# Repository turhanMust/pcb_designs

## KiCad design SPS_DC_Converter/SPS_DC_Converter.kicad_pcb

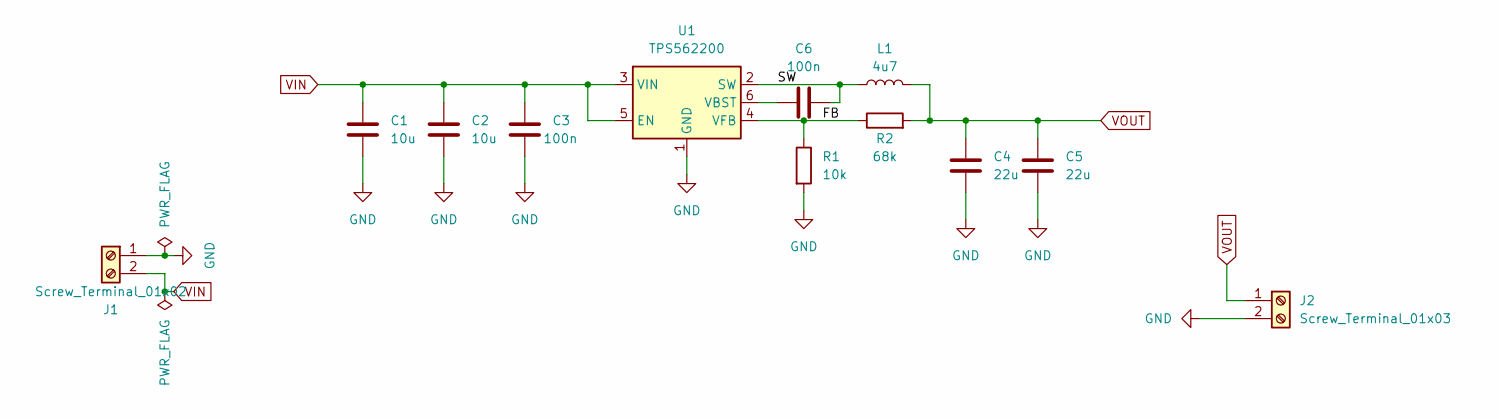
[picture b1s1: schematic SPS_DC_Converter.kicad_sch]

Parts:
C1, C2: 10u; C_0805_2012Metric
C3, C6: 100n; C_0603_1608Metric
C4, C5: 22u; C_1206_3216Metric
J1: Screw_Terminal_01x02; TerminalBlock_bornier-2_P5.08mm
J2: Screw_Terminal_01x03; TerminalBlock_bornier-2_P5.08mm
L1: 4u7; L_Vishay_IHLP-2525
R1: 10k; R_0805_2012Metric
R2: 68k; R_0805_2012Metric
U1: TPS562200; SOT-23-6

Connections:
/FB: R1.1, R2.1, U1.4 (VFB)
/SW: C6.2, L1.1, U1.2 (SW)
GND: C1.2, C2.2, C3.2, C4.2, C5.2, J1.1, J2.2, R1.2, U1.1 (GND)
unnamed: C6.1, U1.6 (VBST)
VIN: C1.1, C2.1, C3.1, J1.2, U1.3 (VIN), U1.5 (EN)
VOUT: C4.1, C5.1, J2.1, L1.2, R2.2

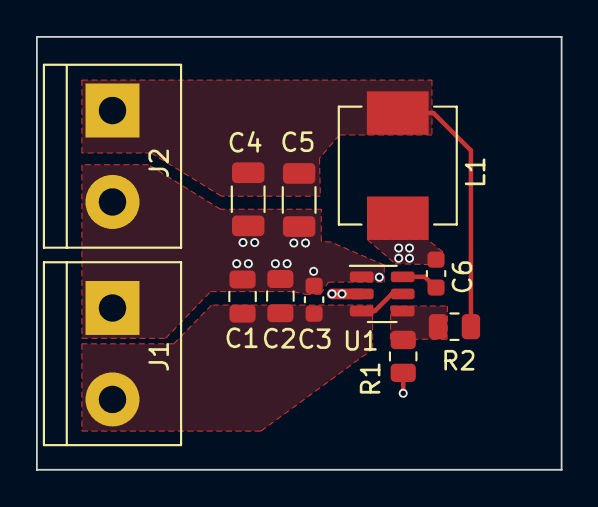
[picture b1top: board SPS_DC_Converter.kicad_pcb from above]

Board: 2 copper layers, 29.1 x 24.0 mm, 12 parts (0 on the bottom side), 6 nets.

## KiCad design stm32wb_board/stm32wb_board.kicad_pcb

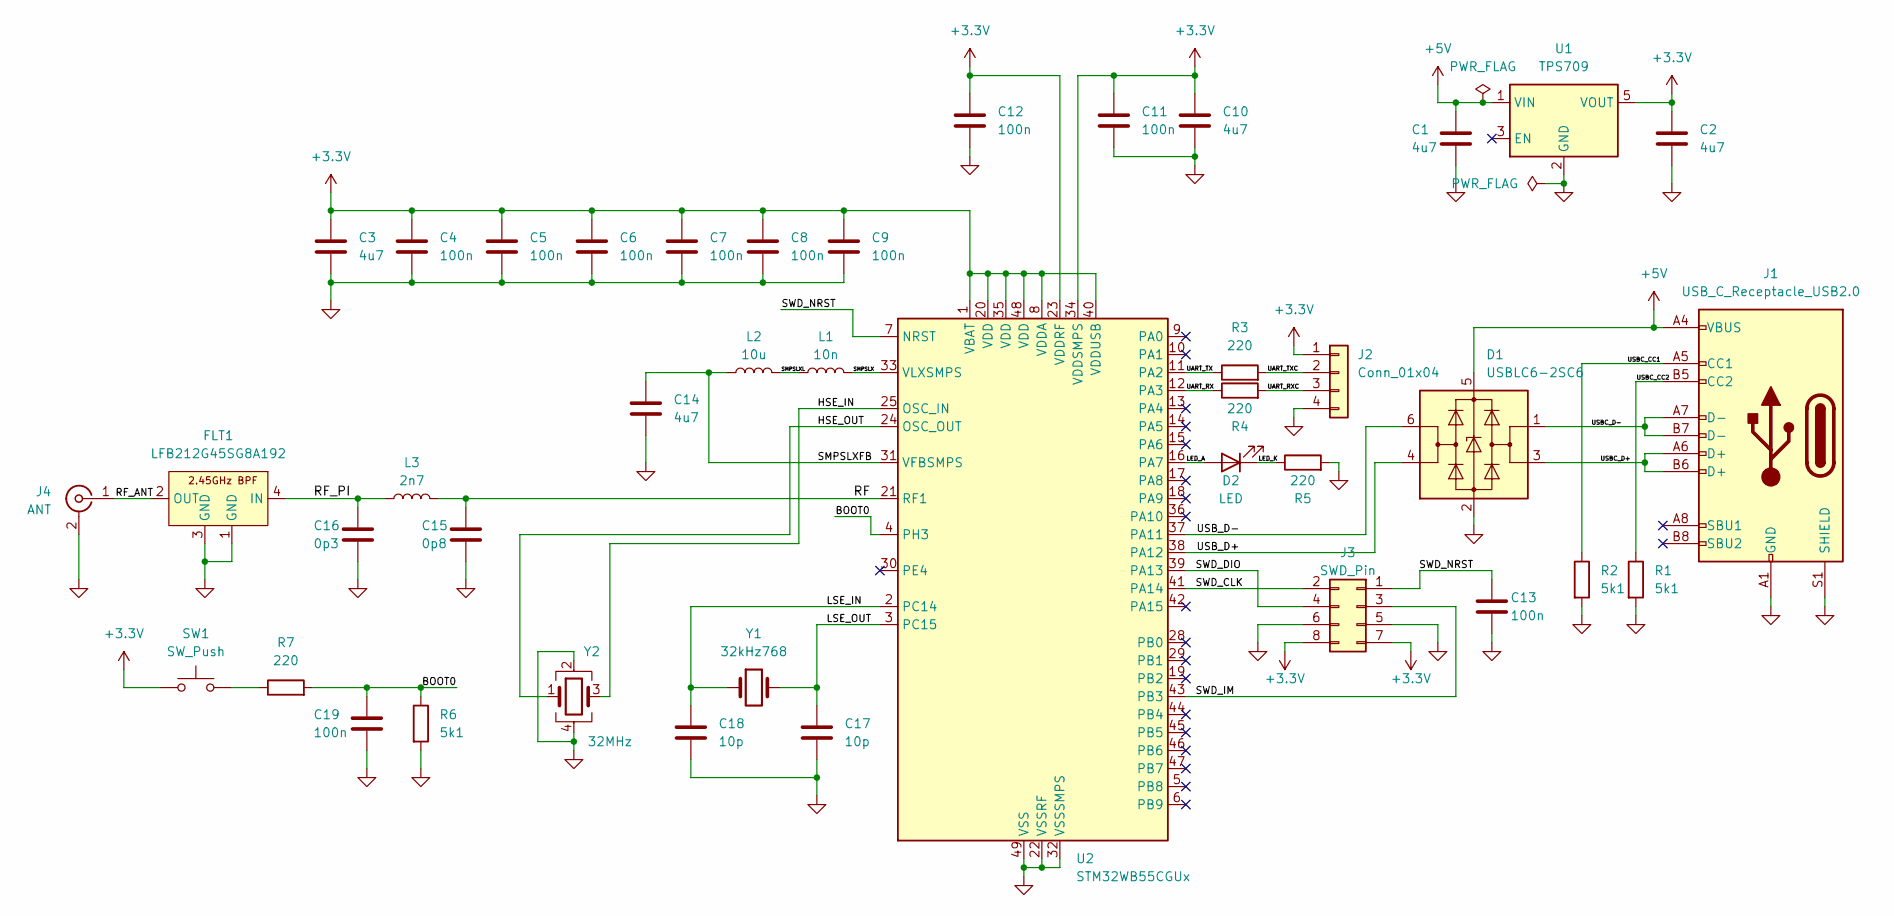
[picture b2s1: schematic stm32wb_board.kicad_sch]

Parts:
C1, C2, C3, C10, C14: 4u7; C_0603_1608Metric
C4, C5, C6, C7, C8, C9, C11, C12, C13, C19: 100n; C_0402_1005Metric
C15: 0p8; C_0603_1608Metric
C16: 0p3; C_0201_0603Metric
C17, C18: 10p; C_0402_1005Metric
D1: USBLC6-2SC6; SOT-23-6
D2: LED; LED_0402_1005Metric
FLT1: LFB212G45SG8A192; LFB21(0805)_SG
J1: USB_C_Receptacle_USB2.0; USB_C_Receptacle_GCT_USB4105-xx-A_16P_TopMnt_Horizontal
J2: Conn_01x04; PinHeader_1x04_P2.54mm_Vertical
J3: SWD_Pin; PinSocket_2x04_P2.54mm_Vertical
J4: ANT; U.FL_Hirose_U.FL-R-SMT-1_Vertical
L1: 10n; L_0402_1005Metric
L2: 10u; L_0805_2012Metric
L3: 2n7; L_0402_1005Metric
R1, R2, R6: 5k1; R_0402_1005Metric
R3, R4, R5, R7: 220; R_0402_1005Metric
SW1: SW_Push; SW_SPST_CK_RS282G05A3
U1: TPS709; SOT-23-5
U2: STM32WB55CGUx; QFN-48-1EP_7x7mm_P0.5mm_EP5.6x5.6mm
Y1: 32kHz768; Crystal_SMD_3215-2Pin_3.2x1.5mm
Y2: 32MHz; Crystal_SMD_2016-4Pin_2.0x1.6mm

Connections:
+3.3V: C2.1, C3.1, C4.1, C5.1, C6.1, C7.1, C8.1, C9.1, C10.1, C11.1, C12.1, J2.1, J3.7, J3.8, SW1.1, U1.5 (VOUT), U2.1 (VBAT), U2.8 (VDDA), U2.20 (VDD), U2.23 (VDDRF), U2.34 (VDDSMPS), U2.35 (VDD), U2.40 (VDDUSB), U2.48 (VDD)
+5V: C1.1, D1.5 (VBUS), J1.A4 (VBUS), J1.A9 (VBUS), J1.B4 (VBUS), J1.B9 (VBUS), U1.1 (VIN)
/BOOT0: C19.1, R6.1, R7.2, U2.4 (PH3)
/HSE_IN: U2.25 (OSC_IN), Y2.3
/HSE_OUT: U2.24 (OSC_OUT), Y2.1
/LED_A: D2.2 (A), U2.16 (PA7)
/LED_K: D2.1 (K), R5.1
/LSE_IN: C18.1, U2.2 (PC14), Y1.1
/LSE_OUT: C17.1, U2.3 (PC15), Y1.2
/RF: C15.1, L3.2, U2.21 (RF1)
/RF_ANT: FLT1.2 (OUT), J4.1 (In)
/RF_PI: C16.1, FLT1.4 (IN), L3.1
/SMPSLX: L1.2, U2.33 (VLXSMPS)
/SMPSLXFB: C14.1, L2.1, U2.31 (VFBSMPS)
/SMPSLXL: L1.1, L2.2
/SWD_CLK: J3.2, U2.41 (PA14)
/SWD_DIO: J3.4, U2.39 (PA13)
/SWD_IM: J3.3, U2.43 (PB3)
/SWD_NRST: C13.1, J3.1, U2.7 (NRST)
/UART_RX: R4.1, U2.12 (PA3)
/UART_RXC: J2.3, R4.2
/UART_TX: R3.1, U2.11 (PA2)
/UART_TXC: J2.2, R3.2
/USBC_CC1: J1.A5 (CC1), R2.1
/USBC_CC2: J1.B5 (CC2), R1.1
/USBC_D+: D1.3 (I/O2), J1.A6 (D+), J1.B6 (D+)
/USBC_D-: D1.1 (I/O1), J1.A7 (D-), J1.B7 (D-)
/USB_D+: D1.4 (I/O2), U2.38 (PA12)
/USB_D-: D1.6 (I/O1), U2.37 (PA11)
GND: C1.2, C2.2, C3.2, C4.2, C5.2, C6.2, C7.2, C8.2, C9.2, C10.2, C11.2, C12.2, C13.2, C14.2, C15.2, C16.2, C17.2, C18.2, C19.2, D1.2 (GND), FLT1.1 (GND), FLT1.3 (GND), J1.A1 (GND), J1.A12 (GND), J1.B1 (GND), J1.B12 (GND), J1.S1 (SHIELD), J2.4, J3.5, J3.6, J4.2 (Ext), R1.2, R2.2, R5.2, R6.2, U1.2 (GND), U2.22 (VSSRF), U2.32 (VSSSMPS), U2.49 (VSS), Y2.2, Y2.4
unnamed: R7.1, SW1.2

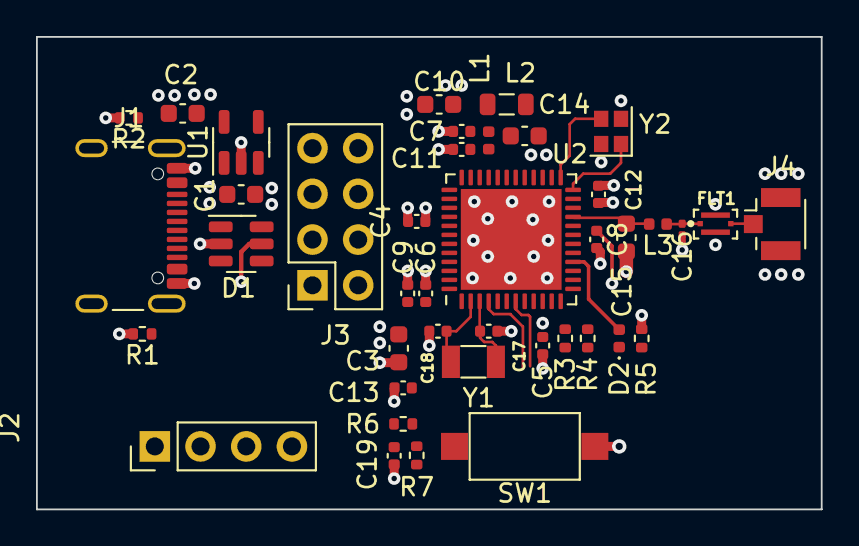
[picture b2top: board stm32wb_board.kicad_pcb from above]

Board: 4 copper layers, 43.6 x 26.2 mm, 41 parts (0 on the bottom side), 31 nets.

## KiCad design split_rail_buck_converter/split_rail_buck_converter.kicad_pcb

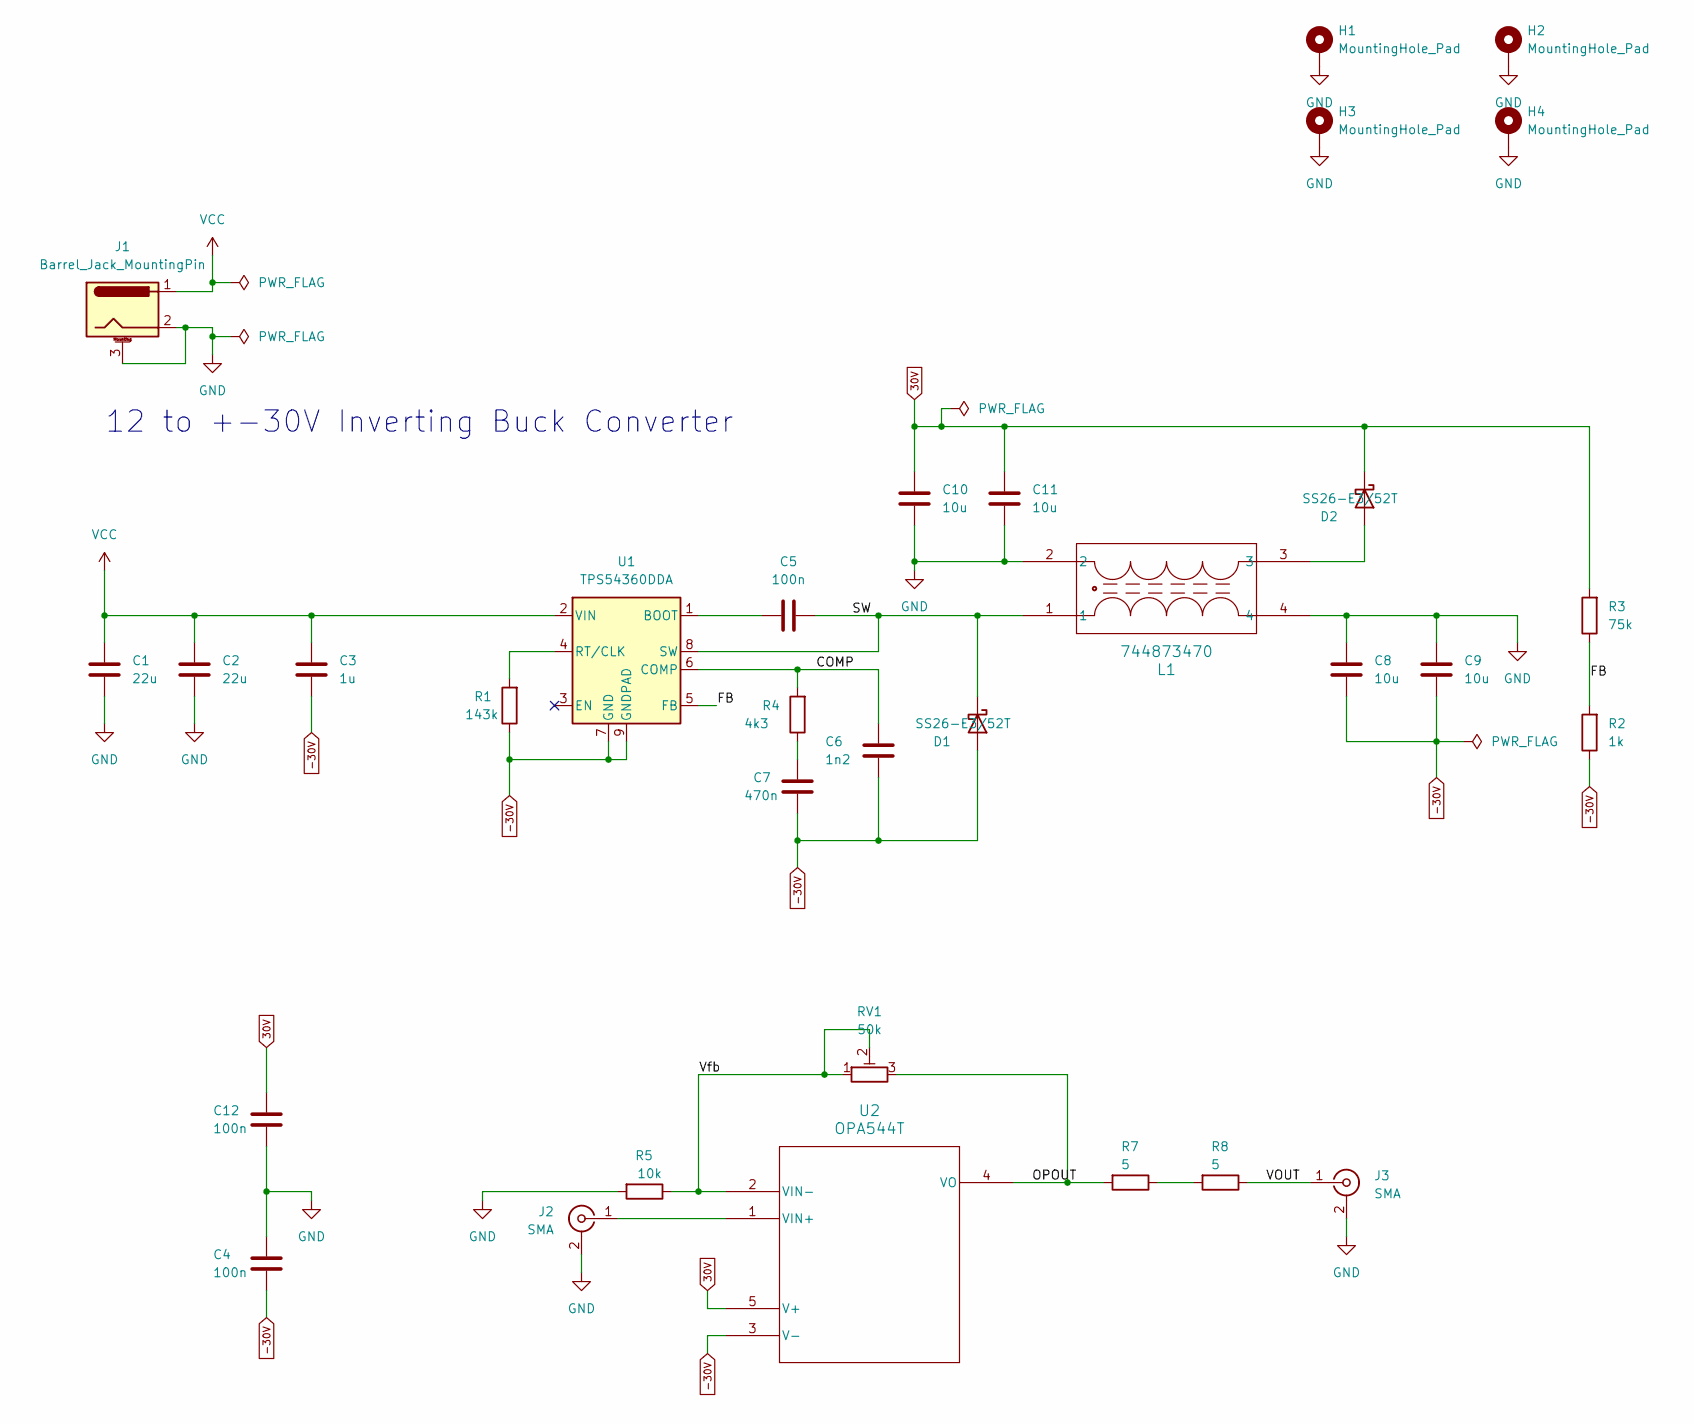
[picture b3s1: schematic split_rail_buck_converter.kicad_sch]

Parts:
C1, C2: 22u; C_1210_3225Metric
C3: 1u; C_0805_2012Metric
C4, C5, C12: 100n; C_0603_1608Metric
C6: 1n2; C_0603_1608Metric
C7: 470n; C_0603_1608Metric
C8, C9, C10, C11: 10u; C_1206_3216Metric
D1, D2: SS26-E3/52T; DIODE_DO214AA_MBRS_VIS
H1, H2, H3, H4: MountingHole_Pad; MountingHole_2.5mm_Pad
J1: Barrel_Jack_MountingPin; BarrelJack_Horizontal
J2, J3: SMA; SMA_Samtec_SMA-J-P-X-ST-EM1_EdgeMount
L1: 744873470; 744873470_WRE
R1: 143k; R_0603_1608Metric
R2: 1k; R_0603_1608Metric
R3: 75k; R_0603_1608Metric
R4: 4k3; R_0603_1608Metric
R5: 10k; R_0603_1608Metric
R7, R8: 5; R_1210_3225Metric
RV1: 50k; Potentiometer_Bourns_3296W_Vertical
U1: TPS54360DDA; TI_SO-PowerPAD-8_ThermalVias
U2: OPA544T; KC5

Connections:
30V: C10.1, C11.1, C12.1, D2.1 (K), R3.2, U2.5 (V+)
-30V: C3.2, C4.2, C6.2, C7.2, C8.2, C9.2, D1.2 (A), R1.1, R2.1, U1.7 (GND), U1.9 (GNDPAD), U2.3 (V-)
/COMP: C6.1, R4.2, U1.6 (COMP)
/FB: R2.2, R3.1, U1.5 (FB)
/OPOUT: R7.2, RV1.3, U2.4 (VO)
/SW: C5.2, D1.1 (K), L1.1, U1.8 (SW)
/VOUT: J3.1 (In), R8.1
/Vfb: R5.1, RV1.1, RV1.2, U2.2 (VIN-)
GND: C1.2, C2.2, C4.1, C8.1, C9.1, C10.2, C11.2, C12.2, H1.1, H2.1, H3.1, H4.1, J1.2, J1.3 (MountPin), J2.2 (Ext), J3.2 (Ext), L1.2, L1.4, R5.2
unnamed: C7.1, R4.1
unnamed: D2.2 (A), L1.3
unnamed: J2.1 (In), U2.1 (VIN+)
unnamed: R7.1, R8.2
unnamed: C5.1, U1.1 (BOOT)
unnamed: R1.2, U1.4 (RT/CLK)
VCC: C1.1, C2.1, C3.1, J1.1, U1.2 (VIN)

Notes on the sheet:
12 to +-30V Inverting Buck Converter

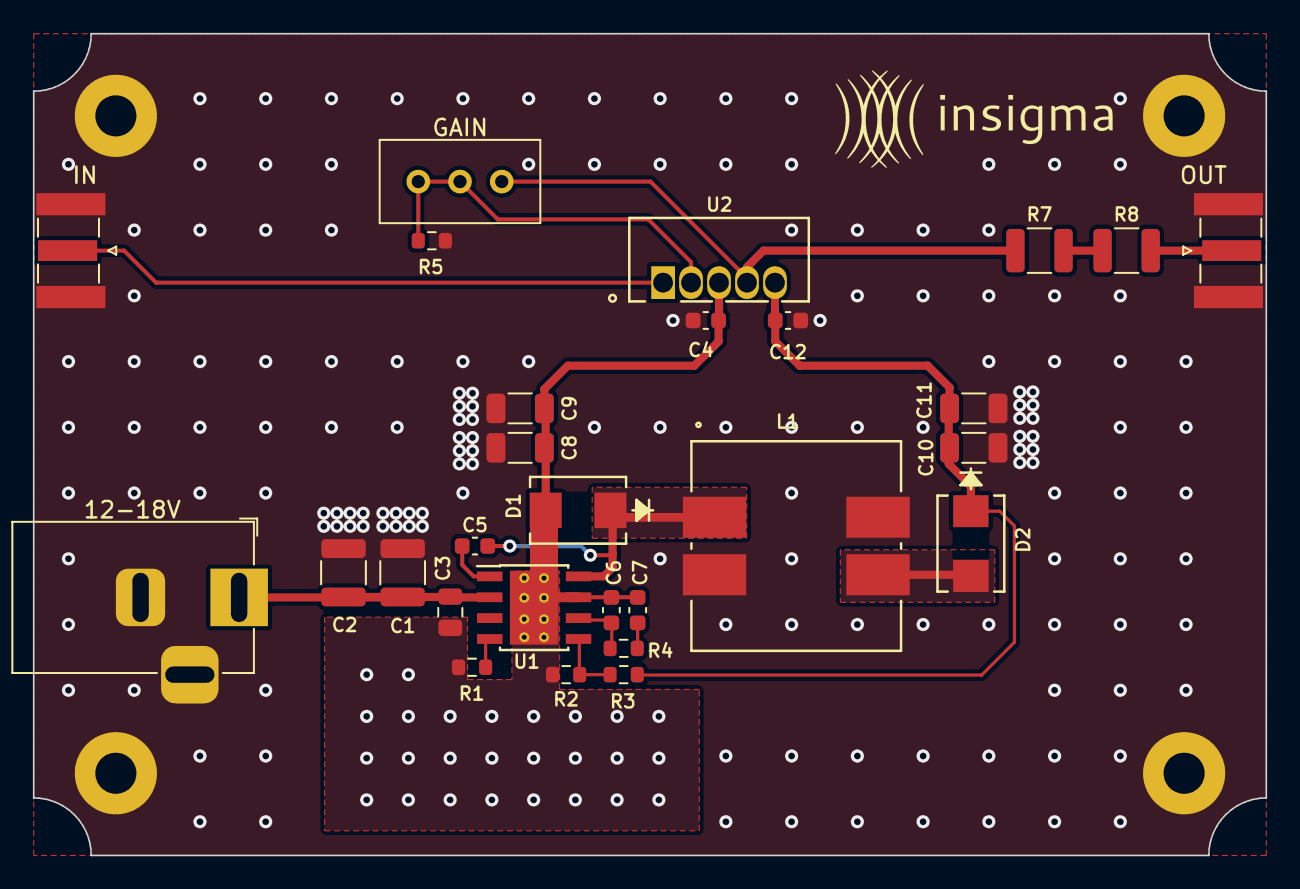
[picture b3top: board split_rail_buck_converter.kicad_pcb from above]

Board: 2 copper layers, 75.0 x 50.0 mm, 32 parts (0 on the bottom side), 16 nets.

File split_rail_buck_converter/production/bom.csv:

Designator,Footprint,Quantity,Value,LCSC Part #
"C1, C2",1210,2,22u,
"C10, C11, C8, C9",1206,4,10u,
"C12, C4, C5",0603,3,100n,
C3,0805,1,1u,
C6,0603,1,1n2,
C7,0603,1,470n,
"D1, D2",DIODE_DO214AA_MBRS_VIS,2,SS26-E3/52T,
J1,BarrelJack_Horizontal,1,Barrel_Jack_MountingPin,
"J2, J3",SMA_Samtec_SMA-J-P-X-ST-EM1_EdgeMount,2,SMA,
L1,744873470_WRE,1,744873470,
R1,0603,1,143k,
R2,0603,1,1k,
R3,0603,1,75k,
R4,0603,1,4k3,
R5,0603,1,10k,
"R7, R8",1210,2,5,
RV1,Potentiometer_Bourns_3296W_Vertical,1,50k,
U1,TI_SO-PowerPAD-8_ThermalVias,1,TPS54360DDA,
U2,KC5,1,OPA544T,

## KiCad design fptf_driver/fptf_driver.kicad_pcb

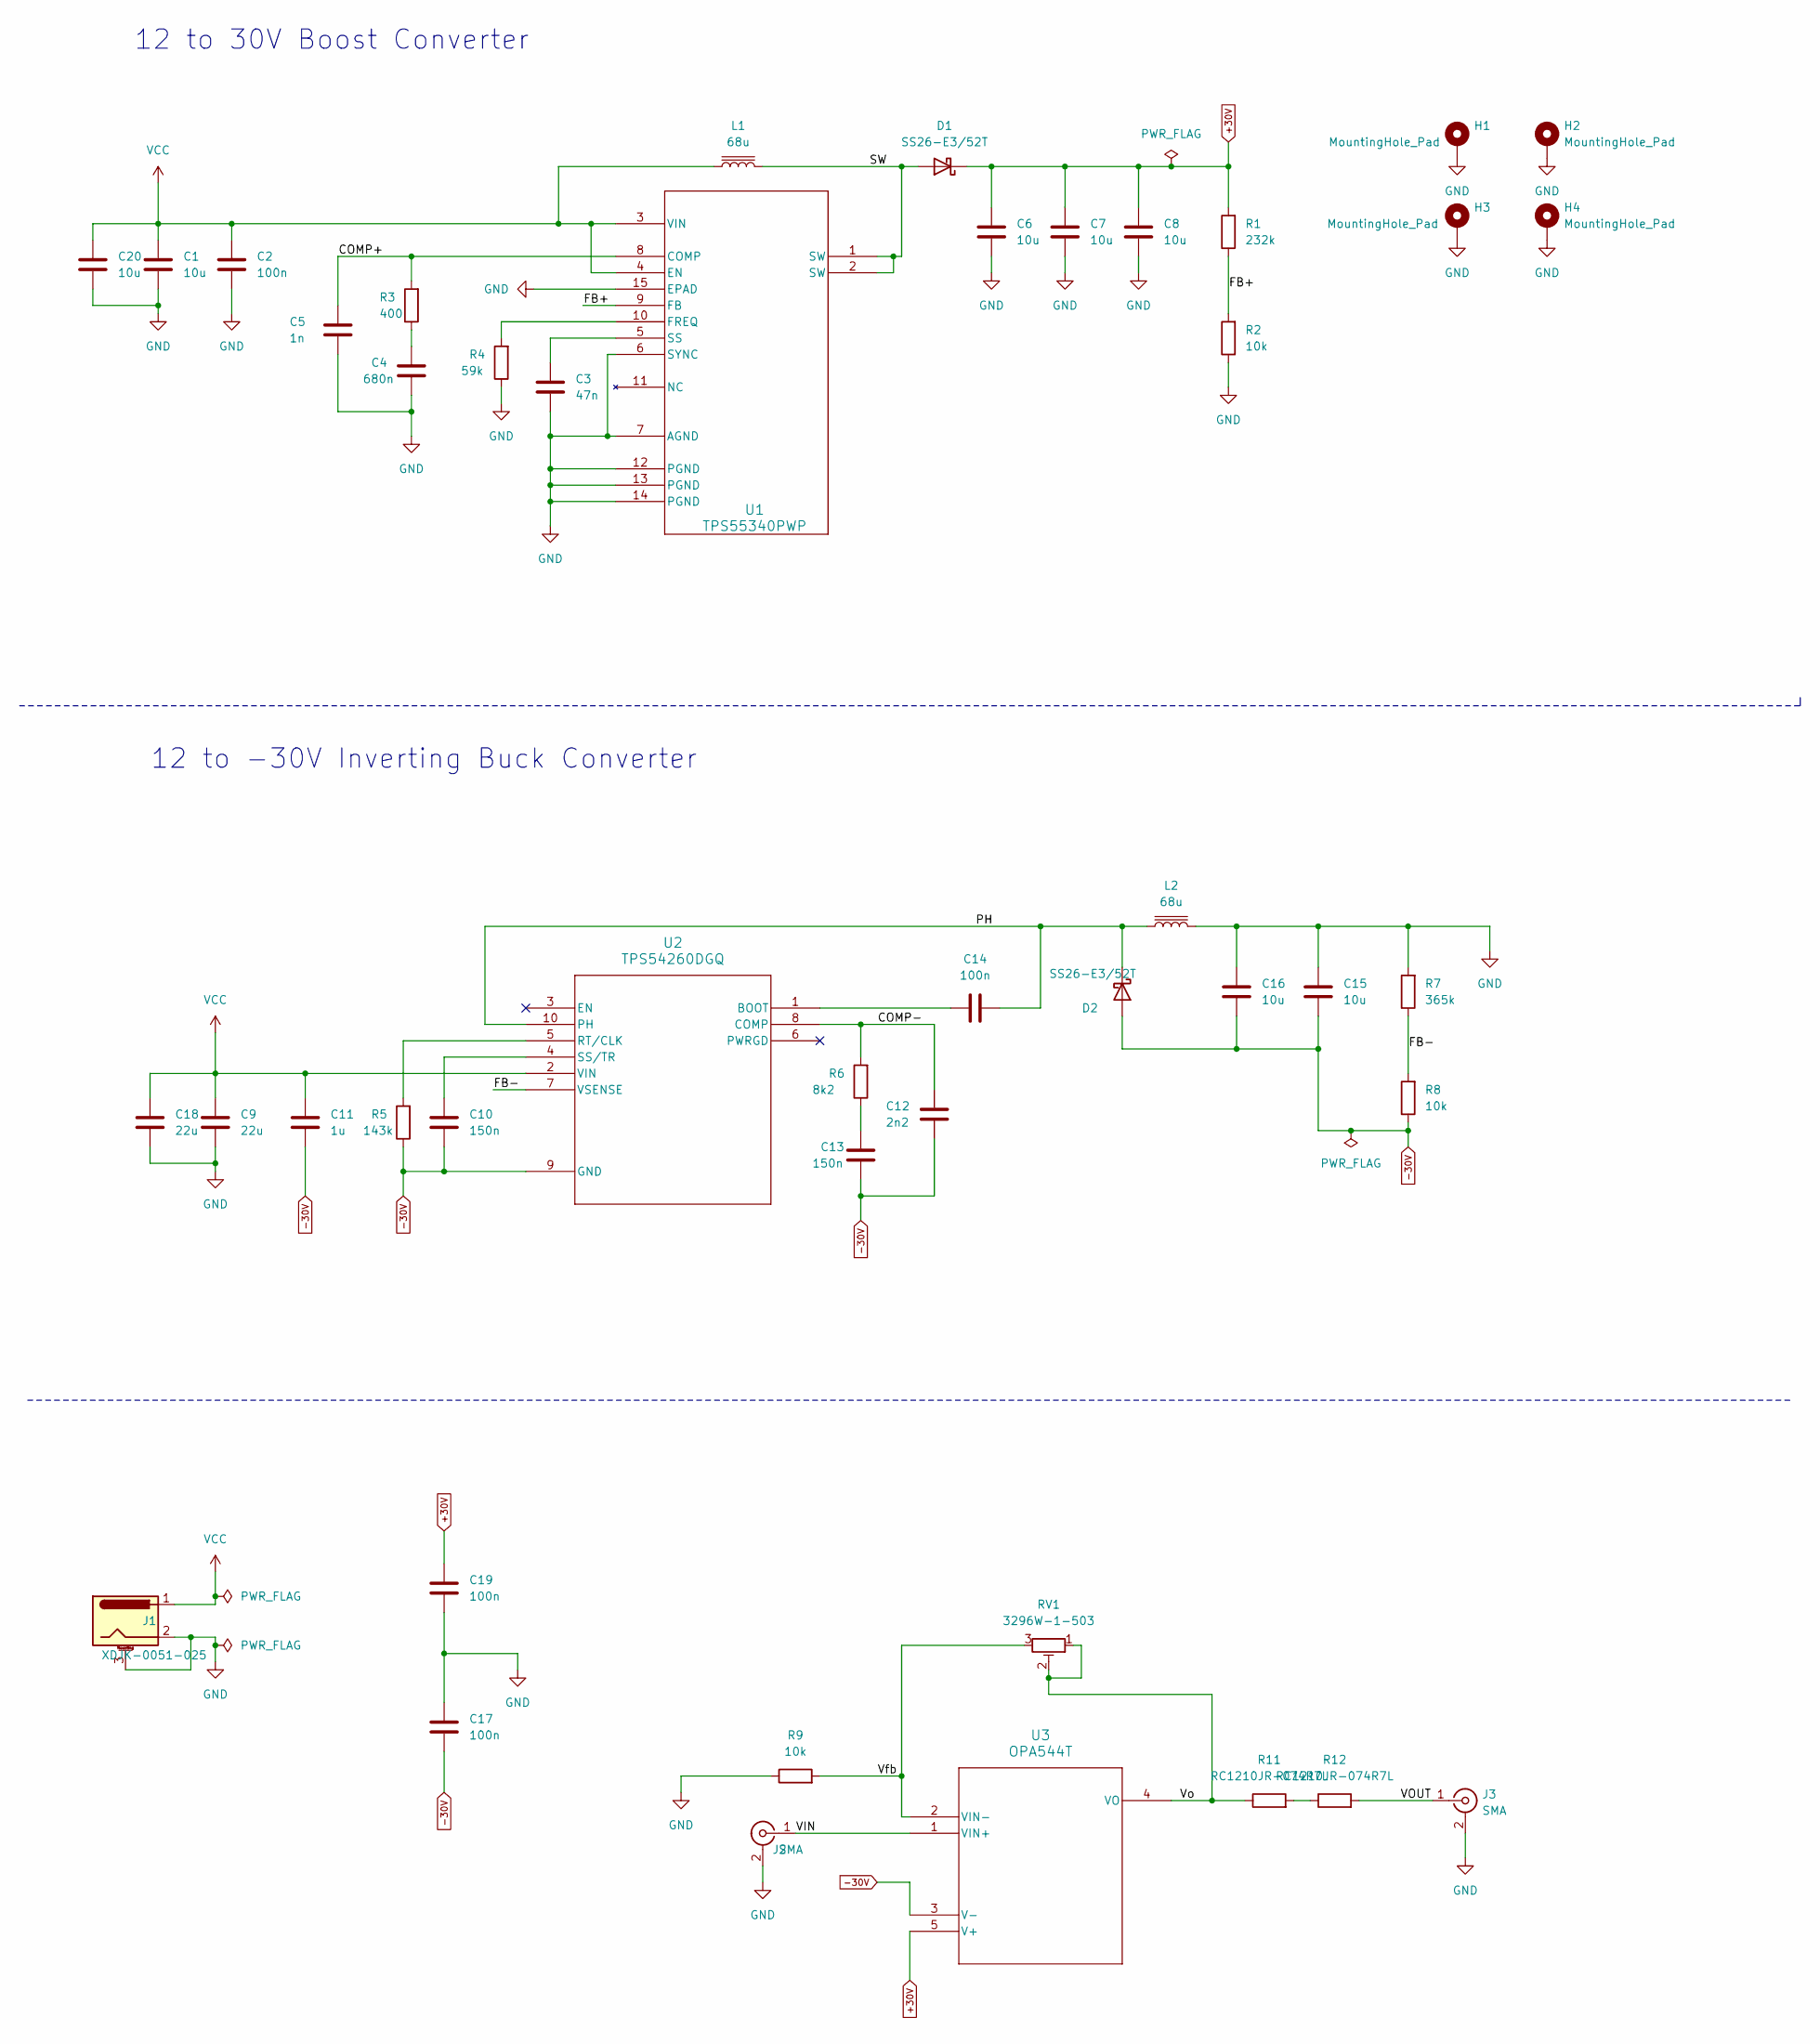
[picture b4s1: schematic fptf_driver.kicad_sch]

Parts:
C1, C6, C7, C8, C15, C16, C20: 10u; C_1206_3216Metric
C2, C14: 100n; C_0603_1608Metric
C3: 47n; C_0603_1608Metric
C4: 680n; C_0603_1608Metric
C5: 1n; C_0603_1608Metric
C9, C18: 22u; C_1210_3225Metric
C10, C13: 150n; C_0603_1608Metric
C11: 1u; C_0603_1608Metric
C12: 2n2; C_0603_1608Metric
C17, C19: 100n; C_1206_3216Metric
D1, D2: SS26-E3/52T; DIODE_DO214AA_MBRS_VIS
H1, H2, H3, H4: MountingHole_Pad; MountingHole_2.5mm_Pad
J1: XDJK-0051-025; BarrelJack_Horizontal
J2, J3: SMA; SMA_Samtec_SMA-J-P-X-ST-EM1_EdgeMount
L1, L2: 68u; IND_1050P-WE-PD_WRE
R1: 232k; R_0603_1608Metric
R2, R8, R9: 10k; R_0603_1608Metric
R3: 400; R_0603_1608Metric
R4: 59k; R_0603_1608Metric
R5: 143k; R_0603_1608Metric
R6: 8k2; R_0603_1608Metric
R7: 365k; R_0603_1608Metric
R11, R12: RC1210JR-074R7L; R_1210_3225Metric
RV1: 3296W-1-503; Potentiometer_Bourns_3296W_Vertical
U1: TPS55340PWP; PWP14
U2: TPS54260DGQ; DGQ10_1P88X1P57
U3: OPA544T; KC5

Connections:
+30V: C6.1, C7.1, C8.1, C19.1, D1.1 (K), R1.2, U3.5 (V+)
-30V: C10.2, C11.2, C12.2, C13.2, C15.2, C16.2, C17.2, D2.2 (A), R5.1, R8.1, U2.9 (GND), U3.3 (V-)
/COMP+: C5.1, R3.2, U1.8 (COMP)
/COMP-: C12.1, R6.2, U2.8 (COMP)
/FB+: R1.1, R2.2, U1.9 (FB)
/FB-: R7.1, R8.2, U2.7 (VSENSE)
/PH: C14.2, D2.1 (K), L2.1, U2.10 (PH)
/SW: D1.2 (A), L1.2, U1.1 (SW), U1.2 (SW)
/VIN: J2.1 (In), U3.1 (VIN+)
/VOUT: J3.1 (In), R12.2
/Vfb: R9.2, RV1.3, U3.2 (VIN-)
/Vo: R11.1, RV1.1, RV1.2, U3.4 (VO)
GND: C1.2, C2.2, C3.2, C4.2, C5.2, C6.2, C7.2, C8.2, C9.2, C15.1, C16.1, C17.1, C18.2, C19.2, C20.2, H1.1, H2.1, H3.1, H4.1, J1.2, J1.3 (MountPin), J2.2 (Ext), J3.2 (Ext), L2.2, R2.1, R4.1, R7.2, R9.1, U1.6 (SYNC), U1.7 (AGND), U1.12 (PGND), U1.13 (PGND), U1.14 (PGND), U1.15 (EPAD)
unnamed: C4.1, R3.1
unnamed: C13.1, R6.1
unnamed: R11.2, R12.1
unnamed: R4.2, U1.10 (FREQ)
unnamed: C3.1, U1.5 (SS)
unnamed: C14.1, U2.1 (BOOT)
unnamed: R5.2, U2.5 (RT/CLK)
unnamed: C10.1, U2.4 (SS/TR)
VCC: C1.1, C2.1, C9.1, C11.1, C18.1, C20.1, J1.1, L1.1, U1.3 (VIN), U1.4 (EN), U2.2 (VIN)

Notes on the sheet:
12 to -30V Inverting Buck Converter
12 to 30V Boost Converter

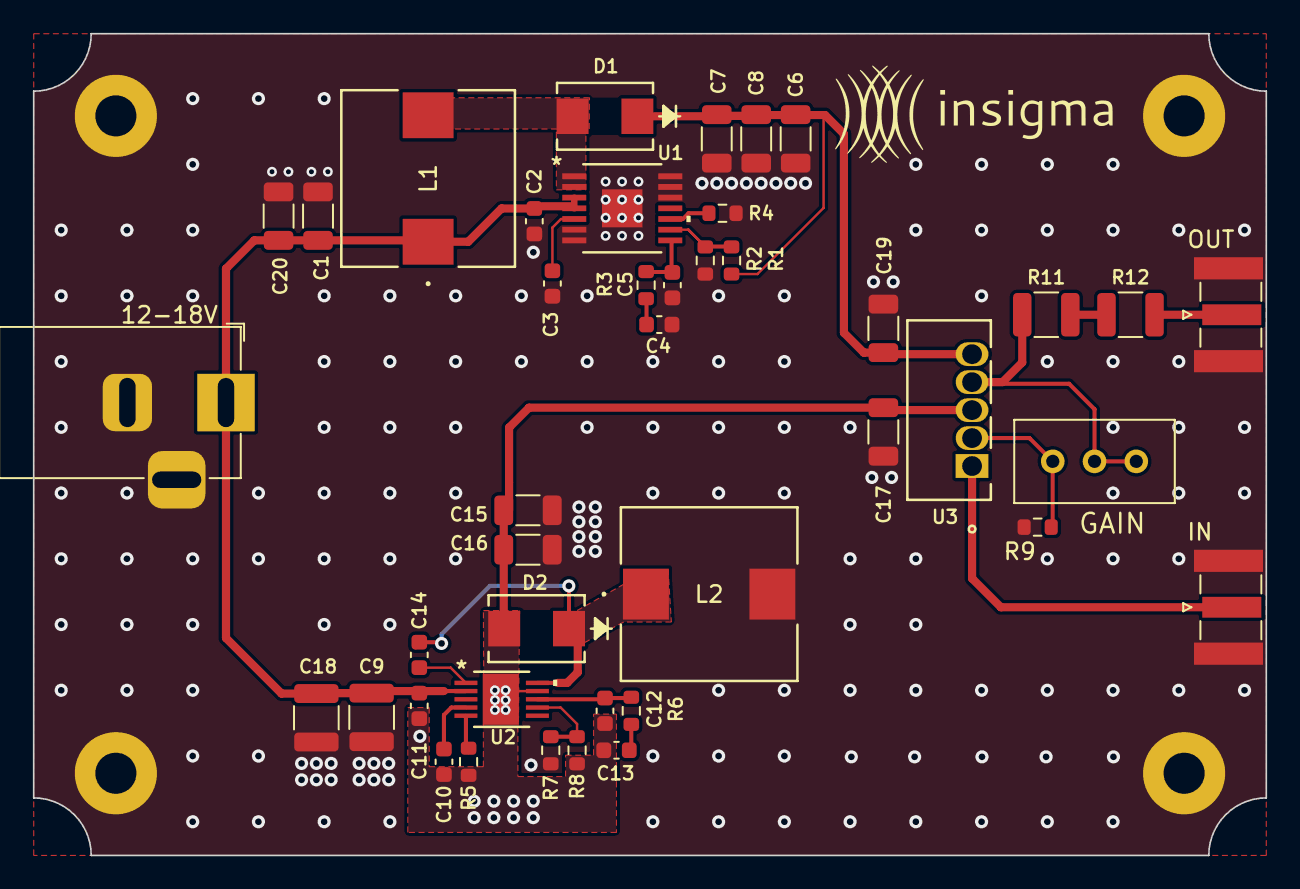
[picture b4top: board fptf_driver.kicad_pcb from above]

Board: 2 copper layers, 75.0 x 50.0 mm, 46 parts (0 on the bottom side), 22 nets.

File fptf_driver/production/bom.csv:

Designator,Footprint,Quantity,Value,LCSC Part #
"C1, C15, C16, C20, C6, C7, C8",1206,7,10u,
"C10, C13",0603,2,150n,
C11,0603,1,1u,
C12,0603,1,2n2,
"C14, C2",0603,2,100n,
"C17, C19",1206,2,100n,
"C18, C9",1210,2,22u,
C3,0603,1,47n,
C4,0603,1,680n,
C5,0603,1,1n,
"D1, D2",DIODE_DO214AA_MBRS_VIS,2,SS26-E3/52T,
J1,BarrelJack_Horizontal,1,XDJK-0051-025,
"J2, J3",SMA_Samtec_SMA-J-P-X-ST-EM1_EdgeMount,2,SMA,
"L1, L2",IND_1050P-WE-PD_WRE,2,68u,
R1,0603,1,232k,
"R11, R12",1210,2,RC1210JR-074R7L,
"R2, R8, R9",0603,3,10k,
R3,0603,1,400,
R4,0603,1,59k,
R5,0603,1,143k,
R6,0603,1,8k2,
R7,0603,1,365k,
RV1,Potentiometer_Bourns_3296W_Vertical,1,3296W-1-503,
U1,PWP14,1,TPS55340PWP,
U2,DGQ10_1P88X1P57,1,TPS54260DGQ,
U3,KC5,1,OPA544T,

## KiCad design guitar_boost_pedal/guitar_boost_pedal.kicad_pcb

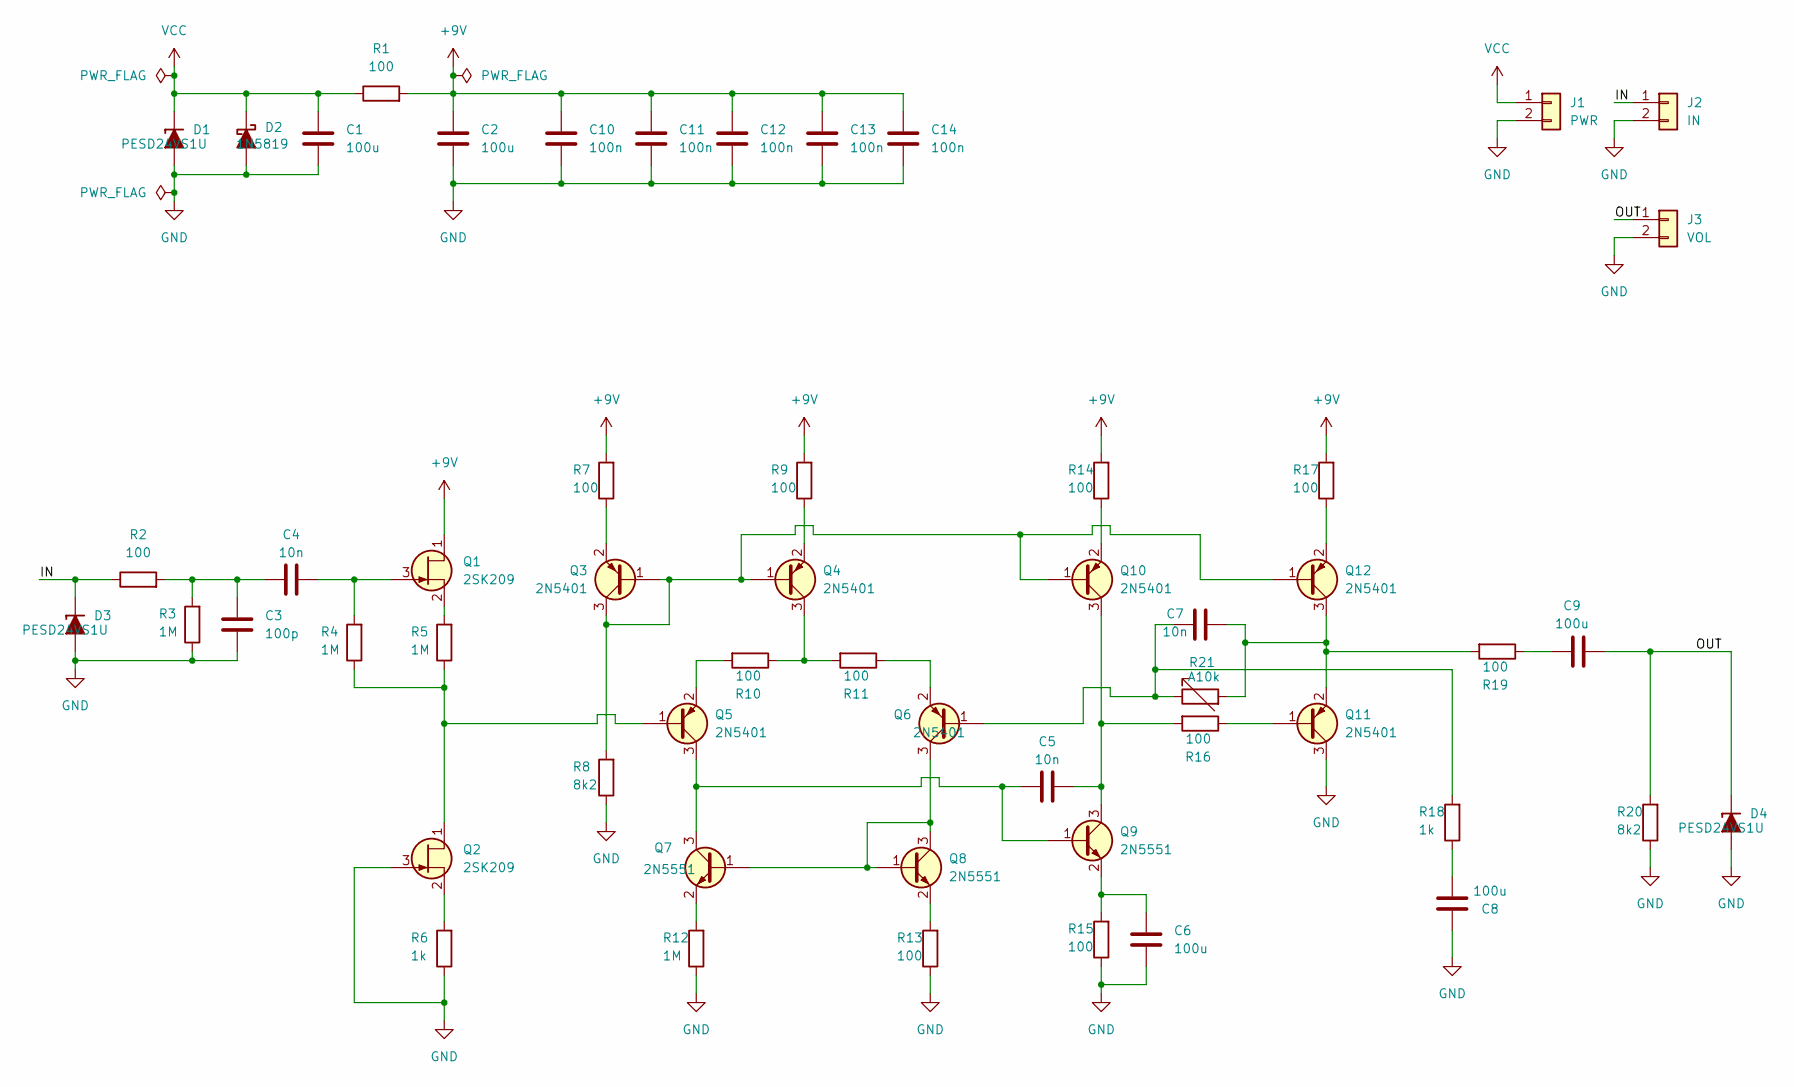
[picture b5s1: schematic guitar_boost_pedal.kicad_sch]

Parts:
C1, C2, C6, C8, C9: 100u; C_1206_3216Metric
C3: 100p; C_0603_1608Metric
C4, C5, C7: 10n; C_0603_1608Metric
C10, C11, C12, C13, C14: 100n; C_0603_1608Metric
D1, D3, D4: PESD24VS1U; D_SOD-523
D2: 1N5819; D_SOD-323
J1: PWR; SolderWire-0.25sqmm_1x02_P4.2mm_D0.65mm_OD1.7mm
J2: IN; SolderWire-0.25sqmm_1x02_P4.2mm_D0.65mm_OD1.7mm
J3: VOL; SolderWire-0.25sqmm_1x02_P4.2mm_D0.65mm_OD1.7mm
Q1, Q2: 2SK209; SC-59
Q3, Q4, Q5, Q6, Q10, Q11, Q12: 2N5401; SOT-23-3
Q7, Q8, Q9: 2N5551; SOT-23
R1, R2, R7, R9, R10, R11, R13, R14, R15, R16, R17, R19: 100; R_0603_1608Metric
R3, R4, R5, R12: 1M; R_0603_1608Metric
R6, R18: 1k; R_0603_1608Metric
R8, R20: 8k2; R_0603_1608Metric
R21: A10k; SolderWire-0.25sqmm_1x02_P4.2mm_D0.65mm_OD1.7mm

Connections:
+9V: C2.1, C10.1, C11.1, C12.1, C13.1, C14.1, Q1.1 (D), R1.2, R7.2, R9.2, R14.2, R17.2
/IN: D3.1 (K), J2.1, R2.1
/OUT: C9.1, D4.1 (K), J3.1, R20.2
GND: C1.2, C2.2, C3.2, C6.2, C8.1, C10.2, C11.2, C12.2, C13.2, C14.2, D1.2 (A), D2.2 (A), D3.2 (A), D4.2 (A), J1.2, J2.2, J3.2, Q2.3 (G), Q11.3 (C), R3.1, R6.1, R8.1, R12.1, R13.1, R15.1, R20.1
unnamed: C3.1, C4.1, R2.2, R3.2
unnamed: C8.2, R18.1
unnamed: C9.2, R19.1
unnamed: C4.2, Q1.3 (G), R4.2
unnamed: Q1.2 (S), R5.2
unnamed: Q2.1 (D), Q5.1 (B), R4.1, R5.1
unnamed: Q2.2 (S), R6.2
unnamed: Q3.2 (E), R7.1
unnamed: Q4.3 (C), R10.1, R11.2
unnamed: Q4.2 (E), R9.1
unnamed: C5.1, Q5.3 (C), Q7.3 (C), Q9.1 (B)
unnamed: Q5.2 (E), R10.2
unnamed: C7.1, Q6.1 (B), R18.2, R21.1
unnamed: Q6.3 (C), Q7.1 (B), Q8.1 (B), Q8.3 (C)
unnamed: Q6.2 (E), R11.1
unnamed: Q7.2 (E), R12.2
unnamed: Q8.2 (E), R13.2
unnamed: C6.1, Q9.2 (E), R15.2
unnamed: Q3.1 (B), Q3.3 (C), Q4.1 (B), Q10.1 (B), Q12.1 (B), R8.2
unnamed: C5.2, Q9.3 (C), Q10.3 (C), R16.2
unnamed: Q10.2 (E), R14.1
unnamed: Q11.1 (B), R16.1
unnamed: C7.2, Q11.2 (E), Q12.3 (C), R19.2, R21.2
unnamed: Q12.2 (E), R17.1
VCC: C1.1, D1.1 (K), D2.1 (K), J1.1, R1.1

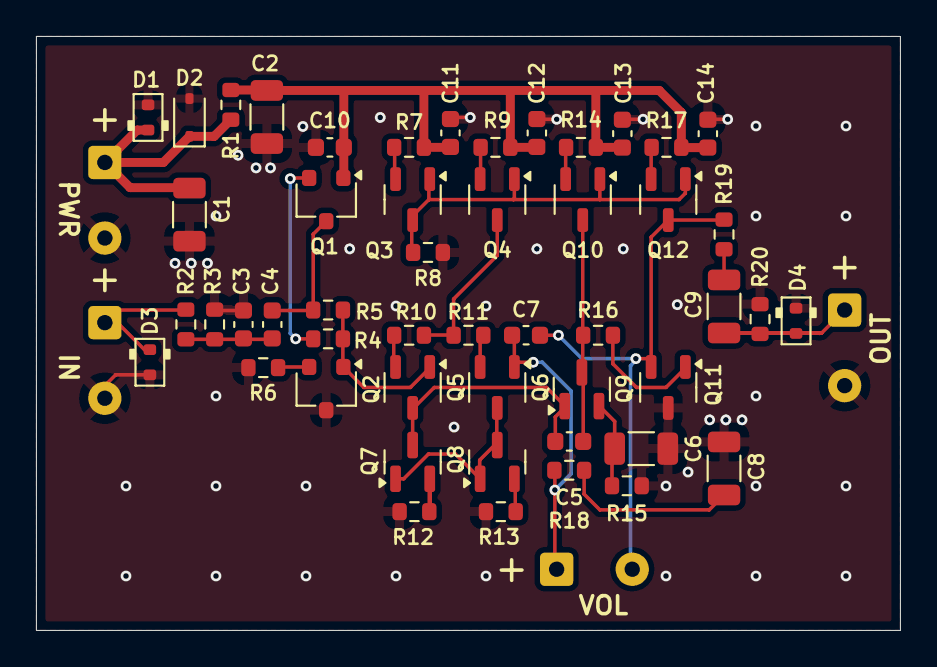
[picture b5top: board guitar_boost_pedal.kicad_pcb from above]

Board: 2 copper layers, 48.0 x 33.0 mm, 54 parts (0 on the bottom side), 29 nets.
